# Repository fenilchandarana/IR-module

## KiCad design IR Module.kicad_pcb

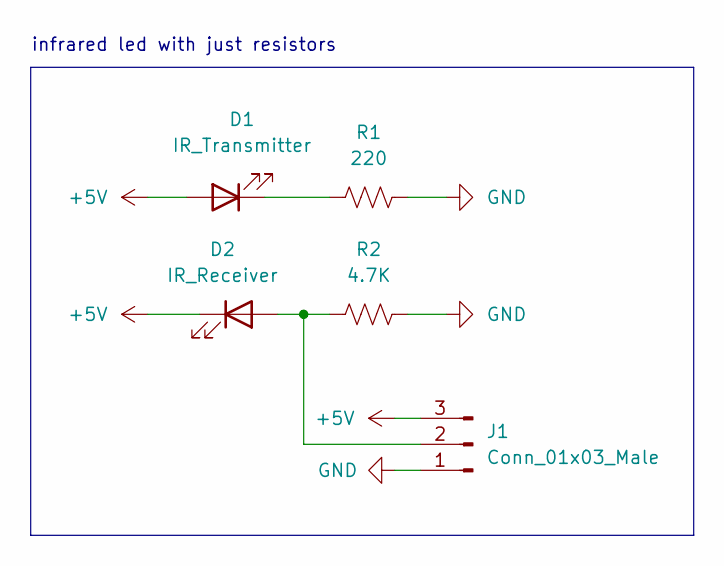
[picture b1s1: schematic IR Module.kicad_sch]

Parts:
D1: IR_Transmitter; LED_D5.0mm
D2: IR_Receiver; LED_D5.0mm
J1: Conn_01x03_Male; PinHeader_1x03_P2.54mm_Vertical
R1: 220; R_Axial_DIN0204_L3.6mm_D1.6mm_P7.62mm_Horizontal
R2: 4.7K; R_Axial_DIN0204_L3.6mm_D1.6mm_P7.62mm_Horizontal

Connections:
+5V: D1.2 (A), D2.1 (K), J1.3
GND: J1.1, R1.2, R2.2
unnamed: D1.1 (K), R1.1
unnamed: D2.2 (A), J1.2, R2.1

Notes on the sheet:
infrared led with just resistors

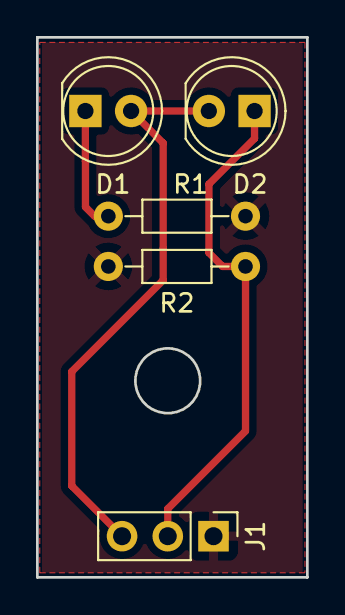
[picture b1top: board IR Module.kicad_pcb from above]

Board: 2 copper layers, 15.0 x 30.0 mm, 5 parts (0 on the bottom side), 4 nets.

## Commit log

2023-03-03 version 1
